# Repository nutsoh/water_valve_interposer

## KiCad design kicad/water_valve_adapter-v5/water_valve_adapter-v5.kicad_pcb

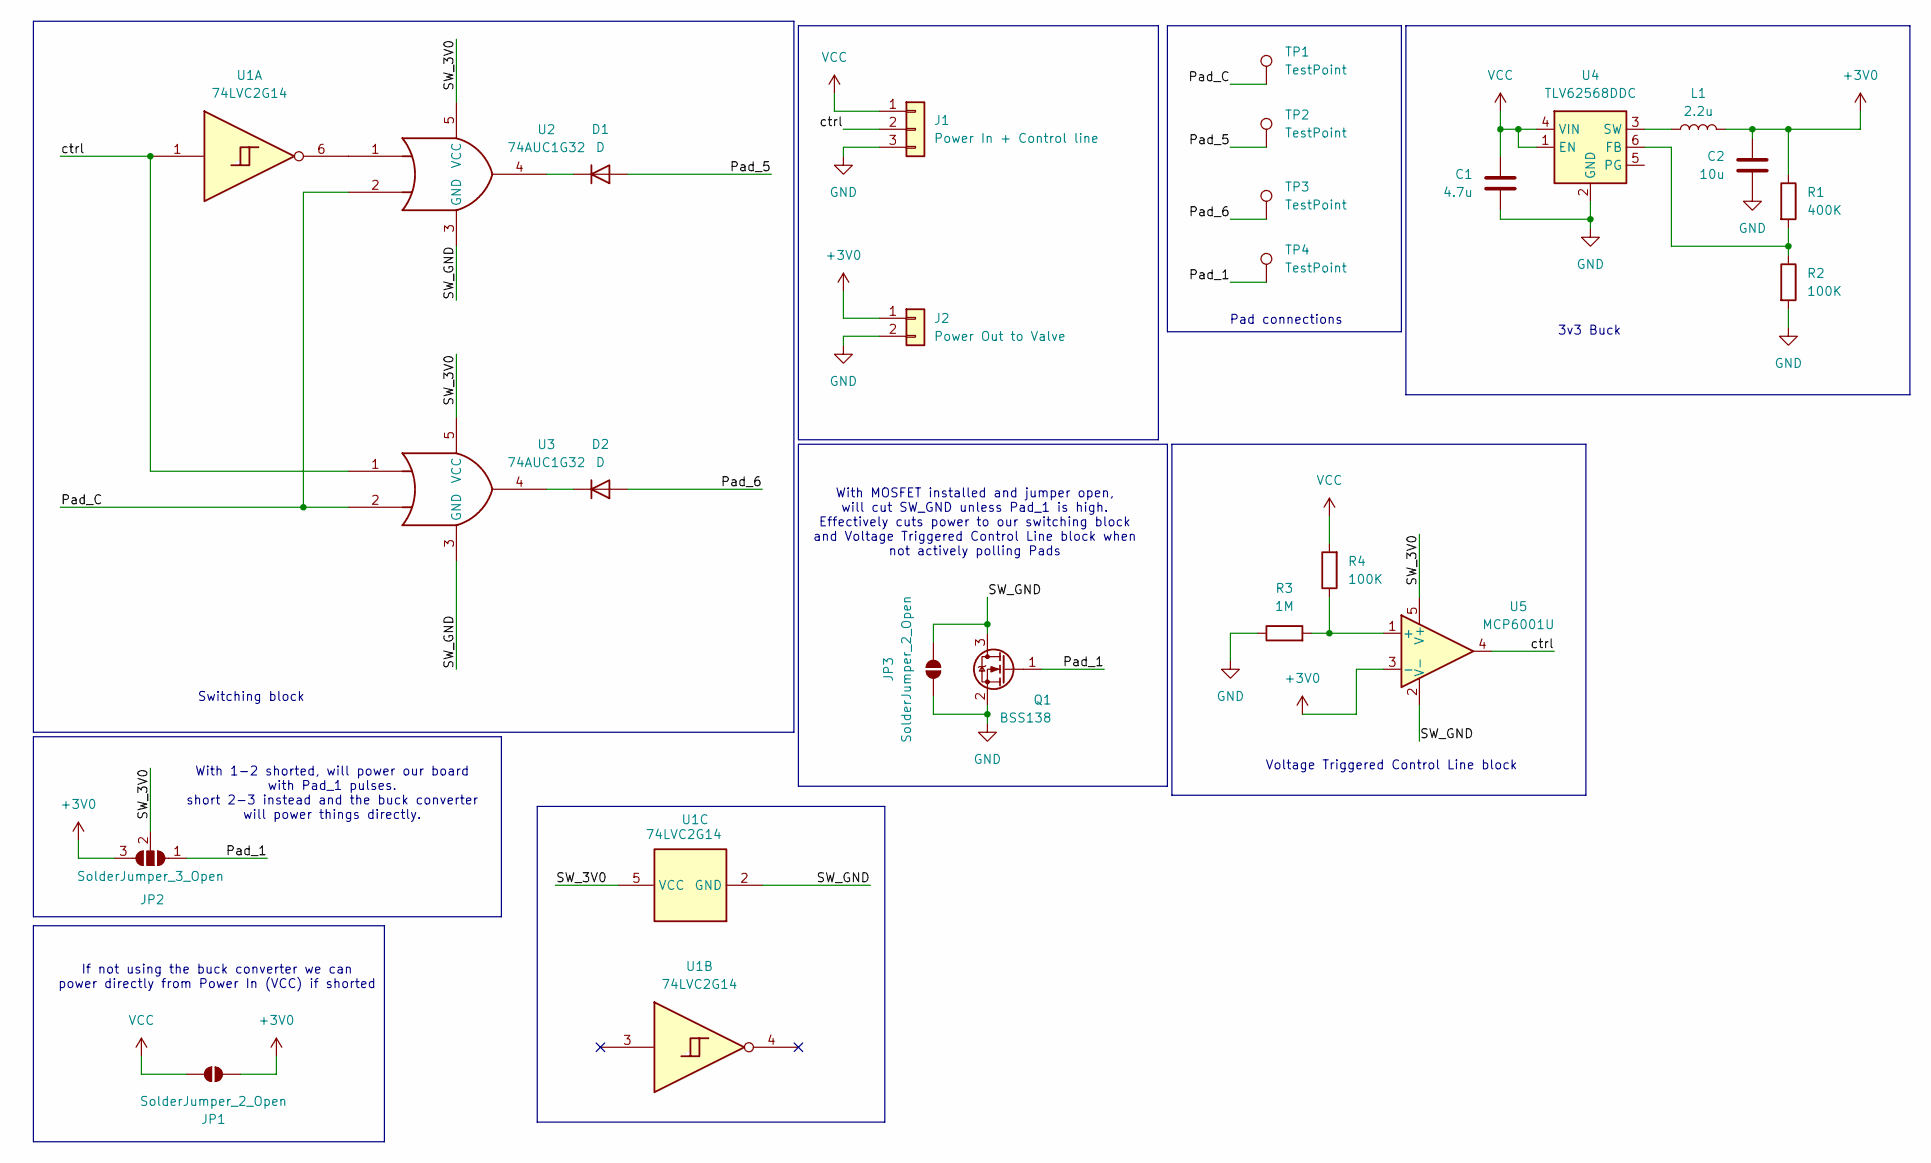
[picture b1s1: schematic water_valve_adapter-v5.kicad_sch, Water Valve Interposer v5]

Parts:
C1: 4.7u; C_0805_2012Metric_Pad1.18x1.45mm_HandSolder
C2: 10u; C_0805_2012Metric_Pad1.18x1.45mm_HandSolder
D1, D2: D; D_SOD-123F
J1: Power In + Control line; Harwin_M20-89003xx_1x03_P2.54mm_Horizontal
J2: Power Out to Valve; R_1020_2550Metric_Pad1.33x5.20mm_HandSolder
JP1, JP3: SolderJumper_2_Open; SolderJumper-2_P1.3mm_Open_RoundedPad1.0x1.5mm
JP2: SolderJumper_3_Open; SolderJumper-3_P1.3mm_Open_RoundedPad1.0x1.5mm
L1: 2.2u; L_Bourns-SRN4018
Q1: BSS138; SOT-23
R1: 400K; R_0805_2012Metric_Pad1.20x1.40mm_HandSolder
R2: 100K; R_0805_2012Metric_Pad1.20x1.40mm_HandSolder
R3: 1M; R_1206_3216Metric_Pad1.30x1.75mm_HandSolder
R4: 100K; R_1206_3216Metric_Pad1.30x1.75mm_HandSolder
TP1, TP2, TP3, TP4: TestPoint; Pad Connector
U1: 74LVC2G14; TSOP-6_1.65x3.05mm_P0.95mm
U2, U3: 74AUC1G32; SOT-353_SC-70-5_Handsoldering
U4: TLV62568DDC; SOT-23-6
U5: MCP6001U; SOT-23-5_HandSoldering

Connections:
+3V0: C2.1, J2.1, JP1.2 (B), JP2.3 (B), L1.2, R1.1, U5.3 (-)
/Pad_1: JP2.1 (A), Q1.1 (G), TP4.1
/Pad_5: D1.2 (A), TP2.1
/Pad_6: D2.2 (A), TP3.1
/Pad_C: TP1.1, U2.2, U3.2
/SW_3V0: JP2.2 (C), U1.5 (VCC), U2.5 (VCC), U3.5 (VCC), U5.5 (V+)
/SW_GND: JP3.1 (A), Q1.3 (D), U1.2 (GND), U2.3 (GND), U3.3 (GND), U5.2 (V-)
/ctrl: J1.2, U1.1, U3.1, U5.4
GND: C1.2, C2.2, J1.3, J2.2, JP3.2 (B), Q1.2 (S), R2.2, R3.1, U4.2 (GND)
unnamed: D1.1 (K), U2.4
unnamed: D2.1 (K), U3.4
unnamed: U1.6, U2.1
unnamed: R1.2, R2.1, U4.6 (FB)
unnamed: L1.1, U4.3 (SW)
unnamed: R3.2, R4.1, U5.1 (+)
VCC: C1.1, J1.1, JP1.1 (A), R4.2, U4.1 (EN), U4.4 (VIN)

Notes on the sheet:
With 1-2 shorted, will power our board with Pad_1 pulses. short 2-3 instead and the buck converter will power things directly.
Pad connections
With MOSFET installed and jumper open, will cut SW_GND unless Pad_1 is high. Effectively cuts power to our switching block and Voltage Triggered Control Line block when not actively polling Pads
3v3 Buck
Switching block
Voltage Triggered Control Line block
If not using the buck converter we can power directly from Power In (VCC) if shorted

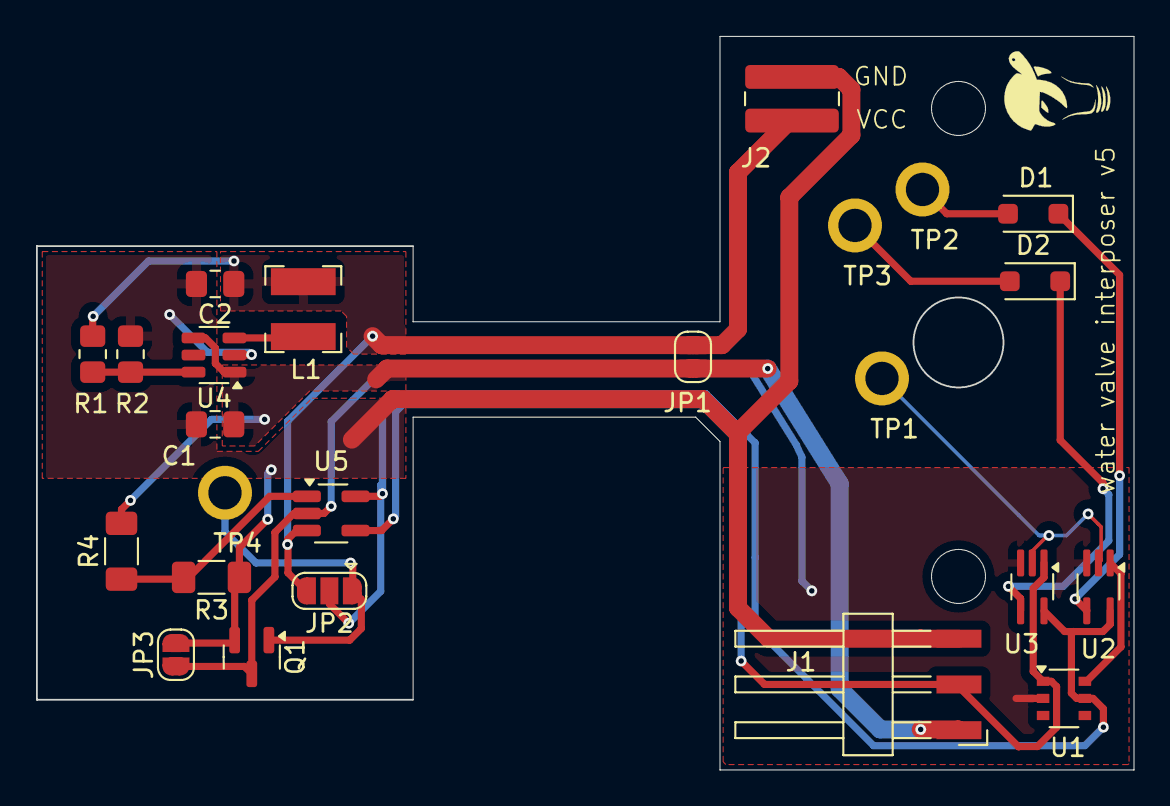
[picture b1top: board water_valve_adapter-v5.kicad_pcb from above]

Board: 2 copper layers, 60.9 x 40.7 mm, 24 parts (0 on the bottom side), 16 nets.

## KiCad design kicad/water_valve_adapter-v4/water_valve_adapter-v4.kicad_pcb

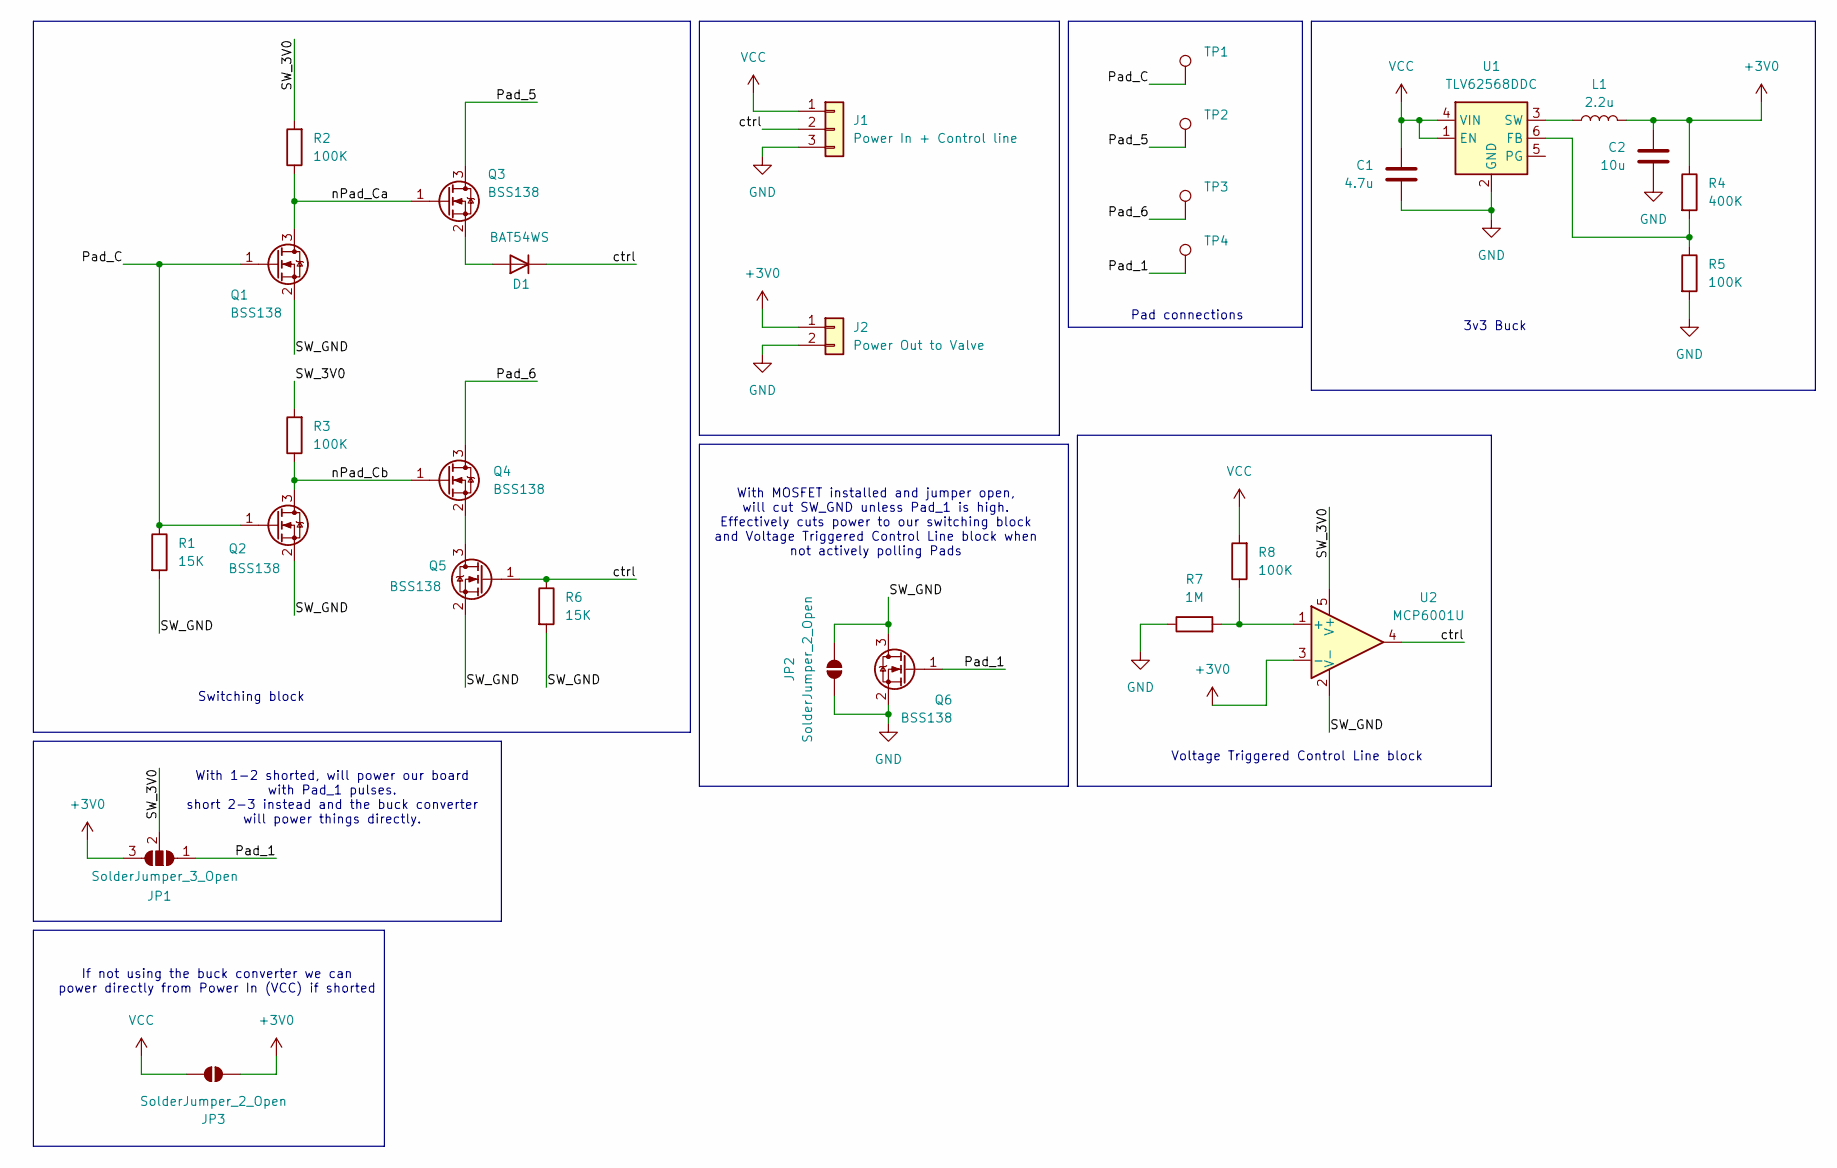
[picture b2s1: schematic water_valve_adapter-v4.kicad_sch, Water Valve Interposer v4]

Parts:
C1: 4.7u; C_0805_2012Metric_Pad1.18x1.45mm_HandSolder
C2: 10u; C_0805_2012Metric_Pad1.18x1.45mm_HandSolder
D1: BAT54WS; D_SOD-123F
J1: Power In + Control line; Harwin_M20-89003xx_1x03_P2.54mm_Horizontal
J2: Power Out to Valve; R_1020_2550Metric_Pad1.33x5.20mm_HandSolder
JP1: SolderJumper_3_Open; SolderJumper-3_P1.3mm_Open_RoundedPad1.0x1.5mm
JP2, JP3: SolderJumper_2_Open; SolderJumper-2_P1.3mm_Open_RoundedPad1.0x1.5mm
L1: 2.2u; L_Bourns-SRN4018
Q1, Q2, Q3, Q4, Q5, Q6: BSS138; SOT-23
R1, R6: 15K; R_1206_3216Metric_Pad1.30x1.75mm_HandSolder
R2, R3, R8: 100K; R_1206_3216Metric_Pad1.30x1.75mm_HandSolder
R4: 400K; R_0805_2012Metric_Pad1.20x1.40mm_HandSolder
R5: 100K; R_0805_2012Metric_Pad1.20x1.40mm_HandSolder
R7: 1M; R_1206_3216Metric_Pad1.30x1.75mm_HandSolder
TP1, TP2, TP3, TP4: TestPoint; Pad Connector
U1: TLV62568DDC; SOT-23-6
U2: MCP6001U; SOT-23-5_HandSoldering

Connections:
+3V0: C2.1, J2.1, JP1.3 (B), JP3.2 (B), L1.2, R4.1, U2.3 (-)
/Pad_1: JP1.1 (A), Q6.1 (G), TP4.1
/Pad_5: Q3.3 (D), TP2.1
/Pad_6: Q4.3 (D), TP3.1
/Pad_C: Q1.1 (G), Q2.1 (G), R1.1, TP1.1
/SW_3V0: JP1.2 (C), R2.2, R3.2, U2.5 (V+)
/SW_GND: JP2.1 (A), Q1.2 (S), Q2.2 (S), Q5.2 (S), Q6.3 (D), R1.2, R6.2, U2.2 (V-)
/ctrl: D1.1 (K), J1.2, Q5.1 (G), R6.1, U2.4
/nPad_Ca: Q1.3 (D), Q3.1 (G), R2.1
/nPad_Cb: Q2.3 (D), Q4.1 (G), R3.1
GND: C1.2, C2.2, J1.3, J2.2, JP2.2 (B), Q6.2 (S), R5.2, R7.1, U1.2 (GND)
unnamed: D1.2 (A), Q3.2 (S)
unnamed: Q4.2 (S), Q5.3 (D)
unnamed: R4.2, R5.1, U1.6 (FB)
unnamed: L1.1, U1.3 (SW)
unnamed: R7.2, R8.1, U2.1 (+)
VCC: C1.1, J1.1, JP3.1 (A), R8.2, U1.1 (EN), U1.4 (VIN)

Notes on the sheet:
If not using the buck converter we can power directly from Power In (VCC) if shorted
3v3 Buck
With 1-2 shorted, will power our board with Pad_1 pulses. short 2-3 instead and the buck converter will power things directly.
Switching block
Pad connections
Voltage Triggered Control Line block
With MOSFET installed and jumper open, will cut SW_GND unless Pad_1 is high. Effectively cuts power to our switching block and Voltage Triggered Control Line block when not actively polling Pads

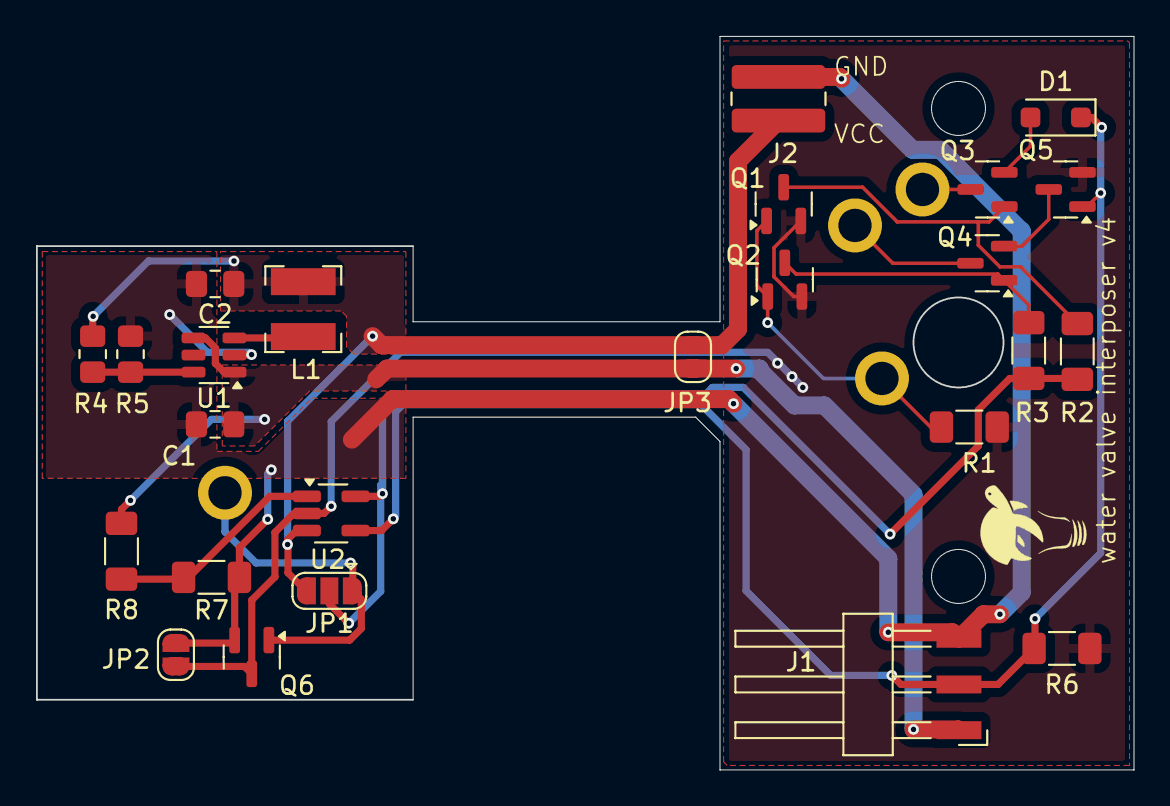
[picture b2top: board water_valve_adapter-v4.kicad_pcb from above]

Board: 2 copper layers, 60.9 x 40.7 mm, 29 parts (0 on the bottom side), 17 nets.

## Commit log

2024-05-05 Adding falstad circuit simulation files
2024-05-28 missed one simulation
2024-06-02 Adding Kicad PCB designs for versions 4 and 5 of the interposer
